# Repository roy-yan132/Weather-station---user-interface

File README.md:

# Embedded Weather Station & User Interface System

## Project Overview

This project is a environment monitoring and interface system based on ESP32-S3.It interfaces ESP32-S3 microcontroller with a BMP280 sensor(I2C), an SPI TFT display(ST7789), and a KY-023 joystick to create this weather station.

The system features the user to navigate the menu using the joystick, displaying real-time atmospheric pressure( hPa and mbar) and temperature. Also, it includes a bonus elevation tracking feature allowing users to adjust the sea-level pressure reference.

## Hardware Architecture & Pin Assignments 

* **Microcontroller:** ESP32-S3-WROOM-2 
* **Sensor:** BMP280 Barometric Pressure and Temperature Sensor 
* **Display:** GMT020-02-7P 2.0-inch SPI TFT LCD (ST7789 Driver) 
* **User Input:** KY-023 Dual-Axis Analog Joystick with Push-Button

| Component | Pin Name | ESP32-S3 GPIO | Function | 
| :--- | :--- | :--- | :--- | 
| **TFT Display** |
| | CS | GPIO 4 | SPI Chip Select | 
| | DC | GPIO 5 | Data/Command | 
| | RST | GPIO 6 | Reset | 
| | SDA (MOSI) | GPIO 11 | SPI Data | 
| | SCL (SCLK) | GPIO 12 | SPI Clock | 
| **BMP280** |
| | SDA | GPIO 8 | I2C Data | 
| | SCL | GPIO 9 | I2C Clock | 
| **Joystick** | 
| | VRx | GPIO 15 | Analog X-axis (Adjust Elevation) | 
| | VRy | GPIO 16 | Analog Y-axis (Menu Navigation) | 
| | SW | GPIO 17 | Push Button (Select/Exit) | 

## Software Architecture

The firmware is developed using PlatformIO in VS Code. It adheres to modular design principles: 
* **Non-blocking Logic:** Uses `millis()` instead of `delay()` for real-time data refreshing and UI transitions, ensuring the joystick remains responsive. 
* **State Machine:** `currentPage` variables manage transitions between the main menu and data display pages. 
* **Debouncing:** Hysteresis thresholds (e.g., `yValue < 500` or `> 3500`) and state tracking (`lastJoyY`) prevent accidental multi-scrolling from a single joystick flick. 

## Engineering Troubleshooting

1. **ESP32-S3-WROOM-2 Flash Configuration Crash:**  

   Initially, the module suffered from a continuous boot loop, throwing an `assert failed: do_core_init startup.c:328` error. This was caused by a mismatch between the default board configuration and the actual hardware capabilities.
   
   **Resolution:** Modified the `platformio.ini` file to explicitly define the correct memory types, setting `board_build.psram_type = opi` and allocating `32MB Flash`. This completely resolved the kernel panic and allowed the system to boot normally.

2. **SPI Bus Congestion & System Crash (Memory/Bus Bottleneck):**  

  While implementing the joystick-based elevation adjustment feature, high-frequency screen redrawing (`drawDataPage()`) caused the SPI bus to become overwhelmed. This led to chip crashes and unexpected white screens.  
  
  **Resolution:** Introduced a boolean state flag (`isAdjusting`). The screen is now only redrawn when the joystick value actually changes (edge detection) or via a non-blocking `millis()` timer. This "redraw-on-demand" approach successfully eliminated bus congestion and prevented system crashes. 

## How to Run 

1. Clone the repository. 
2. Open the project in VS Code with PlatformIO installed. 
3. Build and upload to the ESP32-S3 board. 
4. Use the joystick to navigate the menu (Up/Down to select, Press to enter). 
5. On the Elevation page, use Left/Right to adjust the sea-level pressure reference.

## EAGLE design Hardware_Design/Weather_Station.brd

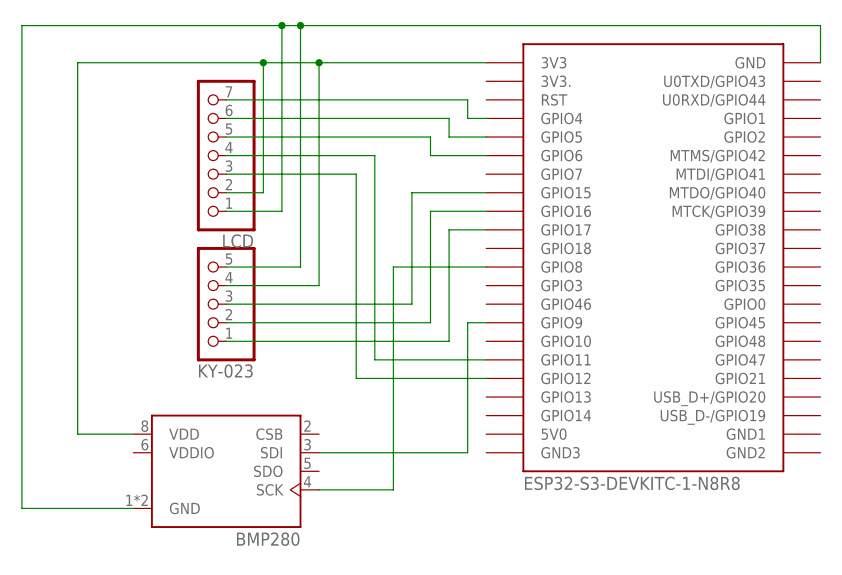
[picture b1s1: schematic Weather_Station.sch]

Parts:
KY-023: PINHD-1X5; 1X05
LCD: PINHD-1X7; 1X07
U1: BMP280; XDCR_BMP280
U$1: ESP32-S3-DEVKITC-1-N8R8

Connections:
3V3.: U$1.J1_2 (3V3.)
5V0: U$1.J1_21 (5V0)
GND1: U$1.J3_21 (GND1)
GND2: U$1.J3_22 (GND2)
GND3: U$1.J1_22 (GND3)
unnamed: LCD.7, U$1.J1_4 (GPIO4)
unnamed: LCD.6, U$1.J1_5 (GPIO5)
unnamed: LCD.5, U$1.J1_6 (GPIO6)
unnamed: KY-023.3, U$1.J1_8 (GPIO15)
unnamed: KY-023.2, U$1.J1_9 (GPIO16)
unnamed: KY-023.1, U$1.J1_10 (GPIO17)
unnamed: KY-023.4, LCD.2, U1.8 (VDD), U$1.J1_1 (3V3)
unnamed: KY-023.5, LCD.1, U1.1 (GND), U1.7 (GND), U$1.J3_1 (GND)
unnamed: U1.4 (SCK), U$1.J1_12 (GPIO8)
unnamed: LCD.4, U$1.J1_17 (GPIO11)
unnamed: LCD.3, U$1.J1_18 (GPIO12)
unnamed: U1.3 (SDI), U$1.J1_15 (GPIO9)
VDDIO: U1.6 (VDDIO)

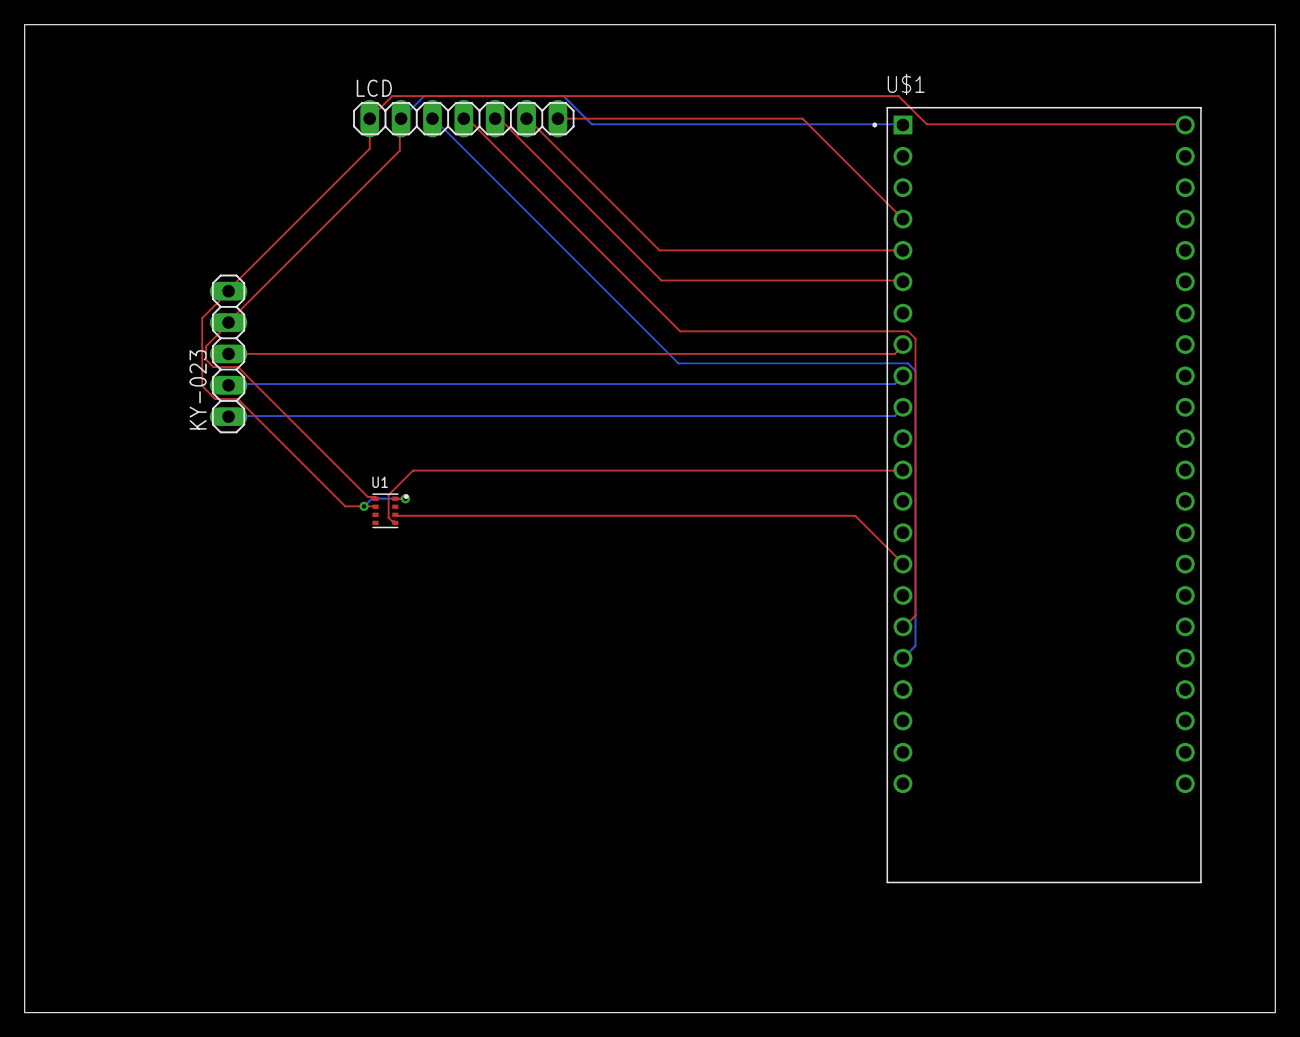
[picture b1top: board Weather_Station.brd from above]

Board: 2 copper layers, 101.3 x 80.0 mm, 4 parts (0 on the bottom side), 12 nets.
